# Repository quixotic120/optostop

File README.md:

# optostop
gen7 optostop

traumflug's optostop for gen 7 electronics. redone with smd components on single side board

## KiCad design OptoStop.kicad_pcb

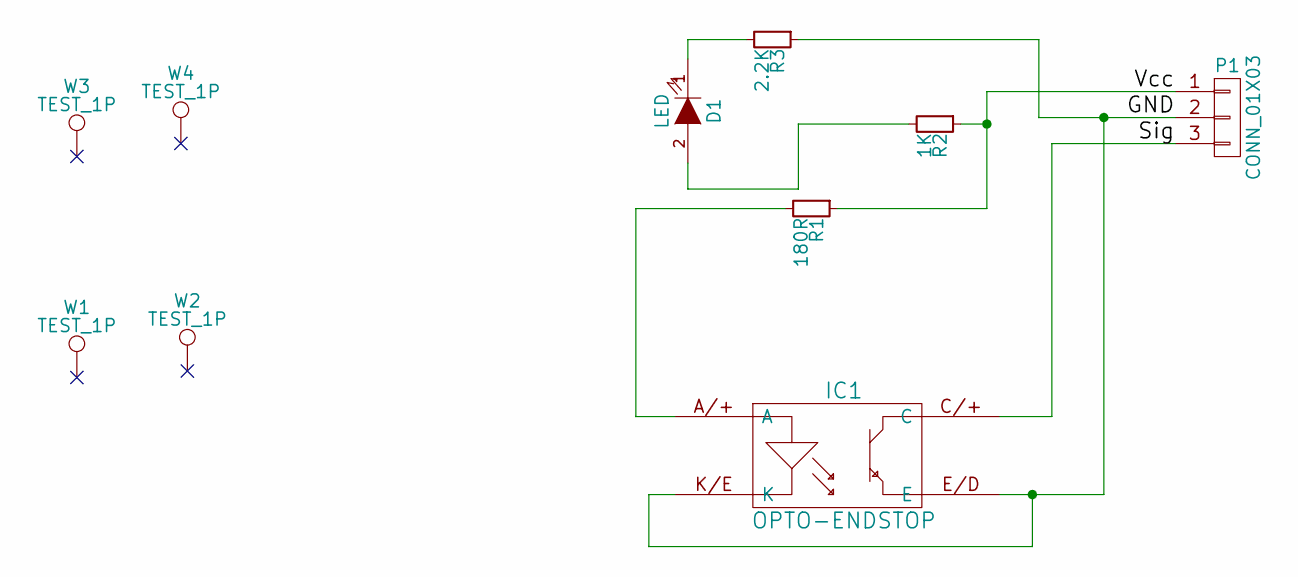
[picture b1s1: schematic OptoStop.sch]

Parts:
D1: LED; LED_0805
IC1: OPTO-ENDSTOP; TCST1103-2103
P1: CONN_01X03; pin_header_2.54mm_1x3
R1: 180R; R_0805
R2: 1K; R_0805
R3: 2.2K; R_0805
W1, W2, W3, W4: TEST_1P; MountingHole_3mm

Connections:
/GND: IC1.E/D (E), IC1.K/E (K), P1.2, R3.1
/Sig: IC1.C/+ (C), P1.3
/Vcc: P1.1, R1.1, R2.1
unnamed: D1.1 (K), R3.2
unnamed: D1.2 (A), R2.2
unnamed: IC1.A/+ (A), R1.2

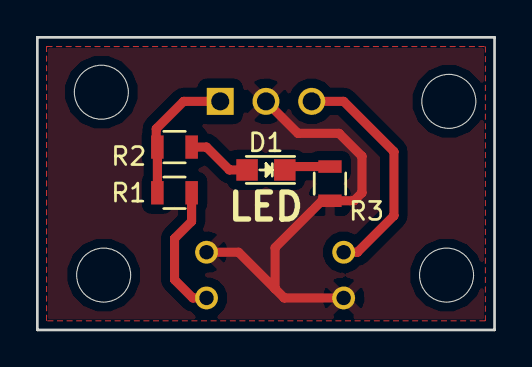
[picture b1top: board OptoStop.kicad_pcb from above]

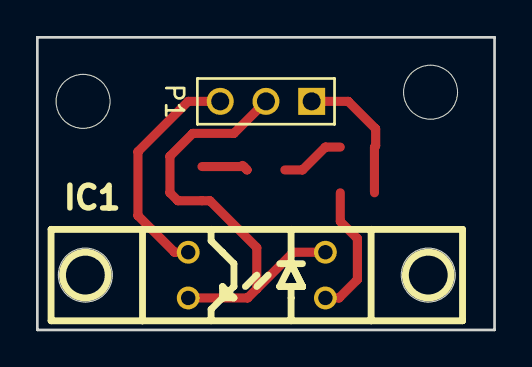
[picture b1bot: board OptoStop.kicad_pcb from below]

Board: 2 copper layers, 25.4 x 16.3 mm, 10 parts (2 on the bottom side), 6 nets.

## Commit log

2016-03-25 gen 7 optostop
    remix of gen7 optostop
2016-03-27 thickened traces
2016-03-27 renders
    made renders and some small updates
2016-03-30 gerbers
